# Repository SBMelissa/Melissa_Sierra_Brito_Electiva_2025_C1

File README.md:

# Melissa_Sierra_Brito_Electiva_2025_C1
Repositorio de Git para la asignatura de Electiva.

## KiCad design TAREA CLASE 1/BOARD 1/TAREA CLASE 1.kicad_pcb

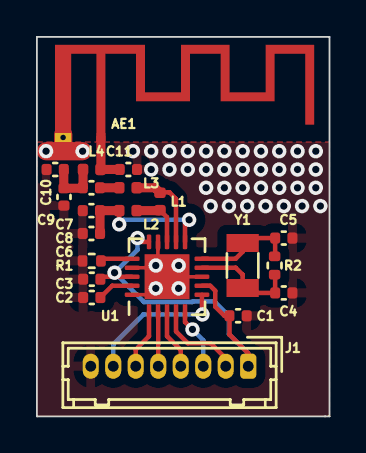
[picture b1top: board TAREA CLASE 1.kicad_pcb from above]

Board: 2 copper layers, 16.3 x 21.1 mm, 21 parts (0 on the bottom side), 18 nets.

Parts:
AE1: Antenna; Texas_SWRA117D_2.4GHz_Right
C1: 10n; C_0402_1005Metric
C2: 33n; C_0402_1005Metric
C3: 1n; C_0402_1005Metric
C4, C5: 22p; C_0402_1005Metric
C6, C8: C_Small; C_0402_1005Metric
C7: 1p5; C_0402_1005Metric
C9: 1p; C_0402_1005Metric
C10, C11: Cx; C_0402_1005Metric
J1: Conn_01x08_Pin; Hirose_DF13-08P-1.25DSA_1x08_P1.25mm_Vertical
L1: 8n2; L_0402_1005Metric
L2: 2n7; L_0402_1005Metric
L3: 3n9; L_0402_1005Metric
L4: Lx; L_0402_1005Metric
R1: 22k; R_0402_1005Metric
R2: 10M; R_0402_1005Metric
U1: NRF24L01; QFN-20-1EP_4x4mm_P0.5mm_EP2.5x2.5mm
Y1: 16MHz; Crystal_SMD_3215-2Pin_3.2x1.5mm

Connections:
GND: C1.2, C2.2, C3.2, C4.2, C5.2, C6.2, C8.2, C9.2, C10.2, C11.2, J1.8, R1.2, U1.8 (VSS), U1.14 (VSS), U1.17 (VSS), U1.20 (VSS)
unnamed: AE1.1 (A), C11.1, L4.2
unnamed: C7.1, L3.2
unnamed: C7.2, C9.1, C10.1, L4.1
unnamed: J1.2, U1.4 (MOSI)
unnamed: J1.3, U1.5 (MISO)
unnamed: J1.4, U1.3 (SCK)
unnamed: J1.5, U1.2 (CSN)
unnamed: J1.6, U1.1 (CE)
unnamed: J1.7, U1.6 (IRQ)
unnamed: L1.1, L3.1, U1.12 (ANT1)
unnamed: L1.2, L2.1, U1.13 (ANT2)
unnamed: C2.1, U1.19 (DVDD)
unnamed: R1.1, U1.16 (IREF)
unnamed: C6.1, C8.1, L2.2, U1.11 (VDD_PA)
unnamed: C5.1, R2.2, U1.10 (XC1), Y1.2
unnamed: C4.1, R2.1, U1.9 (XC2), Y1.1
VDD: C1.1, C3.1, J1.1, U1.7 (VDD), U1.15 (VDD), U1.18 (VDD)

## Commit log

2025-01-23 PRUEBA CARPETA LOCAL
2025-01-24 TAREA SEMANA 1 MITAD
    Tarea semana 1, Tutorial KiCad.
2025-04-28 Practicas de CAD 1
    Cajita freecad
